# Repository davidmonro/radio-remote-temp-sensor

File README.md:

radio-remote-temp-sensor
========================

Code for a temperature sensor which publishes temperatures over a 2.4GHz radio

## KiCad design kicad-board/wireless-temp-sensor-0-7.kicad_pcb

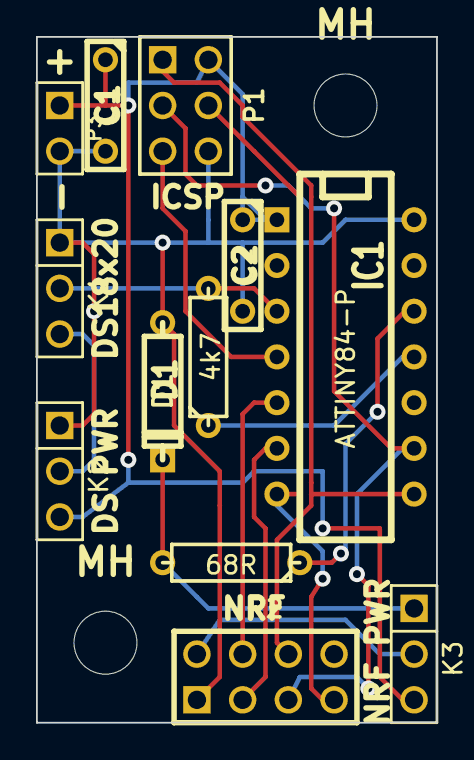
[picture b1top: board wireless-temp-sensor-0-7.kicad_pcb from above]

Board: 2 copper layers, 22.2 x 38.1 mm, 14 parts (0 on the bottom side), 14 nets.

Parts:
C1: 1uF; C2
C2: 100nF; C2
D1: 1N4729A; D3
IC1: ATTINY84-P; DIP-14__300
K1, K2, K3: CONN_3; PIN_ARRAY_3X1
MH: MountingHole_3-5mm_RevA_Date21Jun2010
MH#2: MountingHole_3-5mm_RevA_Date21Jun2010
P1: CONN_3X2; pin_array_3x2
P2: CONN_4X2; pin_array_4x2
P3: CONN_2; PIN_ARRAY_2X1
R1: 68R; R3
R2: 4k7; R3

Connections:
GND: C1.2, C2.2, D1.1, IC1.14, K1.1, K2.1, P1.6, P2.1, P3.2
unnamed: IC1.4, P1.5
unnamed: IC1.9, P1.3, P2.5
unnamed: IC1.7, P1.4, P2.7
unnamed: IC1.8, P1.1, P2.6
unnamed: K3.2, P2.2
unnamed: D1.2, K3.1, R1.2
unnamed: IC1.11, R2.1
unnamed: IC1.3, K1.2, R2.2
unnamed: K1.3, K2.2
unnamed: IC1.6, P2.3
unnamed: IC1.5, P2.4
unnamed: IC1.12, R1.1
VCC: C1.1, C2.1, IC1.1, K2.3, K3.3, P1.2, P3.1

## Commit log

2014-10-01 Push the attiny code
2014-10-01 Add the arduino receiver code
2016-02-22 Tweak some of the radio calls Allow more than 2 sensors Force sensors to 12 bit precision and save in the eeprom
    Add kicad files for the board
